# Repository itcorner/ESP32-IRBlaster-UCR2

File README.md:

# ESP32 IR blaster for the Unfolded Circle Remote Two.

This project implements the [Unfolded Circle Remote Two](https://www.unfoldedcircle.com/) dock API to add additional IR blasters
to your remote setup.

This allows the installation of an IR blaster in an independant location from where your
remote and charging dock are located. For example, in an equipment rack or cupboard, or for
multi-room setups.

⚠️ Since Unfolded Circle has released their dock firmware I have not yet updated the software in this repo for Hardware v0.3. Use koeblaster brach in [this repo](https://github.com/itcorner/ucd2-firmware/tree/koeblaster) in the meanwhile.

## Requirements

1. An [Unfolded Circle Remote Two](https://www.unfoldedcircle.com/).
1. An supported ESP32 hardware (see Section [Supported Electronics](#supported-electronics))
1. [PlatformIO](https://platformio.org/) to build and upload firmware
1. Depending on used hardware: Some basic soldering / breadboarding skills and basic understanding of electronic.
1. Depending on used hardware: Some basic electronic parts and IR led.

## Getting Started

1. Clone project from Github and add to PlatformIO.
2. Select the build environment matching your dock hardware.
    - Add your specific board to ``platformio.ini``. Feel free to contribute this back as a pull-request.
3. If required, modify pin mappings in ``lib/config/blaster_config.h``, or by setting `-D defines` in the ``build_flags`` section of your build environment in ``platformio.ini``, respectively (see section [Customizing Pinout/Configuration](#customizing-pinout-configuration)).
    -  For enabling the *learning of IR codes* make sure you have added ``-DBLASTER_ENABLE_IR_LEARN=true`` to the build_flags of your used PlatformIO environment (or in blaster_config.h) and check the assigned GPIO pin.
    -  **Note:** IR learning feature is still under development and tested only with some basic IR codes.
4. Build *firmware* and *filesystem image* via PlattformIO actions for your target hardware.
5. Upload *firmware* and *filesystem image* to your ESP32 hardware (**Hint:** make sure no serial monitor is active during filesystem upload, otherwise upload will fail!).
    -  Details about SPIFFS filesystem image can be found in the respective [Section](#spiffs-filesystem-image)
6. Start discovering process on your Remote Two. The dock should be detected.
7. Perform setup process for dock via Remote Two.
8. Check serial logging for debugging.

⚠️ Do not forget to select the dock as "IR output device" in the configuration of your remotes!

## Customizing Pinout/Configuration 

The following defines are available in ``lib/config/blaster_config.h`` and can be overwritten by setting ``build_flags`` in ``platformio.ini``.

| Define | Description | Options |
|:-------|:------------|:--------|
|`BLASTER_INDICATOR_MODE` | Defines the type of indicator led used for custom dock | `INDICATOR_OFF` no indicator led available<br/>`INDICATOR_LED` single color led (__default__)<br/>`INDICATOR_PIXEL` digital RGB neopixel led |
|`BLASTER_PIN_INDICATOR` | Defines GPIO pin where indicator led is connected to  | Default: `5`<br/>Has no effect if `BLASTER_INDICATOR_MODE=INDICATOR_OFF` |
|`BLASTER_ENABLE_IR_INTERNAL` | Enables/Disables internal IR channel of dock | `true` channel is enabled (__default__)<br/> `false` channel is disabled |
|`BLASTER_PIN_IR_INTERNAL` | Defines GPIO pin of internal IR channel | Default: `12`<br/>Has no effect if `BLASTER_ENABLE_IR_INTERNAL=false` |
|`BLASTER_ENABLE_IR_OUT_1` | Enables/Disables external IR channel 1 of dock | `true` channel is enabled (__default__)<br/> `false` channel is disabled |
|`BLASTER_PIN_IR_OUT_1` | Defines GPIO pin of external IR channel 1 | Default: `13`<br/>Has no effect if `BLASTER_ENABLE_IR_OUT_1=false` |
|`BLASTER_ENABLE_IR_OUT_2` | Enables/Disables external IR channel 2 of dock | `true` channel is enabled (__default__)<br/> `false` channel is disabled |
|`BLASTER_PIN_IR_OUT_2` | Defines GPIO pin of external IR channel 2 | Default: `14`<br/>Has no effect if `BLASTER_ENABLE_IR_OUT_2=false` |
|`BLASTER_ENABLE_IR_LEARN` | Enables/Disables learning of IR codes by an IR receiver | `true` learning is enabled<br/> `false` learning is disabled  (__default__)|
|`BLASTER_PIN_IR_LEARN` | Defines GPIO pin IR receiver is connected to | Default: `16`<br/>Has no effect if `BLASTER_ENABLE_IR_LEARN=false` |
|`BLASTER_ENABLE_ETH` | Enables/Disables an wired Ethernet interface<br/>Currently only Olimex Boards supported. | `true` Ethernet interface available. Requires definition of `OLIMEX_ESP`<br/> `false` Ethernet interface not available  (__default__)|
|`OLIMEX_ESP` | Defines ESP32 package used in Olimex POE Board<br/>Impacts the pins for ethernet interface | `WROOM` tested and confirmed working<br/>`WROVER` untested ⚠️, therefore breaks build on purpose. Adaption in `eth_service.cpp` required!<br/>Has no effect if `BLASTER_ENABLE_ETH=false` |
|`BLASTER_ENABLE_OTA` | Enables Arduino OTA flashing.<br/>**Note**: This OTA function has nothing to do with firmware updates via Remote Two! | `true` OTA flashing is enabled <br/>`false` OTA flashing is not enabled (__default__)| 

## SPIFFS Filesystem Image

For providing details about the dock via a web user interface, files stored in an SPIFF file system are used.
The actual content of the SPIFFS filesystem image is the `data` directory of the project.

`data/spiffs_manifest.json` holds an index about all available files and their expected MD5 sums.
During boot, the dock will check availability of all files listed in the index and validate their checksum.

⚠️ Currently, the `fs_service` will only allow access to files mentioned in the index and available in the filesystem image, irrespecive of the checksum validataion. This might change in future.

**Hint:** In `tools/update_spiffs_manifest.py` a Python script is available to update the contents and MD5-checksums of the filesystem image index. Make sure the script is executed from the project's main folder.

# Supported Electronics

## KoeBlaster Hardware

*KoeBlaster* is designed to be a drop-in replacement of the Logitech Harmony Hub PCB working with Remote Two.

Schematic is tested and working. Comments are of course appreciated!

PCB is manufactured and working. 

[Manufacturing Data](kicad/KoeBlaster/exports) is available in the repository.

⚠️ When manufacturing, make sure you are using a **PCB height of 1mm**, as otherwise the mounting inside the Harmony Hub are not fitting. ⚠️

### Change History

| Revision | Changes | Known-Issues | 
|:-------|:------------|:------------|
| 0.3 | Supporting SMD or THT leds, split top and side led control, optimized BOM for JLCPCB manufacturing | none (yet) |
| 0.2 | fixes of hw problems from v0.1 | none (yet) |
| 0.1 | initial design | value of current limitation resistors for IR leds too high.<br/>short-circuits on external blaster sockets.<br/>CH340 outputs voltages higher than 3.3V, therefore problems with hardware reset circuit. |

### Schematic

### Board

#### Top

#### Bottom

## Olimex ESP32-PoE-ISO + MOD-IRDA

Olimex offers some nice modules for people wanting Plug&Play solutions. 
Using the PlattformIO Environment `env:olimex_poe_iso` the pins shall already be pre-configured correctly for use with the MOD-IRDA extension board.

⚠️ From Olimex two IRDA add-ons are available (MOD-IRDA and MOD-IRDA+). Only MOD-IRDA is supported by this project! Due to different interfacing MOD-IRDA+ add-on is not compatible! ⚠️

### Customizing the pinout 

If you need to change the pinout feel free to do so. Here are the pins configured for the Olimex Board per default:

| Setting | Description |
|:-------|:------------|
|`BLASTER_INDICATOR_MODE` = `INDICATOR_OFF` | Olimex Board does not offer a led for custom usage, therfore indicator is turned off | 
|`BLASTER_ENABLE_IR_INTERNAL` = `true` | Enables internal IR channel of dock used by MOD-IRDA add-on |
|`BLASTER_PIN_IR_INTERNAL` = `4` | GPIO 4 is wired to UEXT header and used by IR sender on MOD-IRDA add-on |
|`BLASTER_ENABLE_IR_OUT_1` = `false` | Disables external IR channel 1 of dock by default. <br/>If you plan to add external circuity set to `true` and configure `BLASTER_PIN_IR_OUT_1` accordingly (only `GPIO0-31` are supproted) |
|`BLASTER_ENABLE_IR_OUT_2` = `false` | Disables external IR channel 2 of dock by default. <br/>If you plan to add external circuity set to `true` and configure `BLASTER_PIN_IR_OUT_2` accordingly (only `GPIO0-31` are supproted) |
|`BLASTER_ENABLE_IR_LEARN` = `true`  | Enables learning of IR codes by an IR receiver | 
|`BLASTER_PIN_IR_LEARN` = `36` | GPIO 36 is wired to UEXT header and used by IR receiver on MOD-IRDA add-on |
|`BLASTER_ENABLE_ETH` = `true` | Enables the wired Ethernet interface of Olimex board | 
|`OLIMEX_ESP` = `WROOM` | Defines ESP32 package used in Olimex POE Board. Currently only `WROOM` is tested and confirmed working<br/>`WROVER` untested ⚠️, therefore breaks build on purpose. Adaption in `eth_service.cpp` required!<br/>Has no effect if `BLASTER_ENABLE_ETH=false` |

### Links to Olimex product pages

[Olimex PoE Iso Board](https://www.olimex.com/Products/IoT/ESP32/ESP32-POE-ISO/open-source-hardware)

[Olimex MOD-IRDA](https://www.olimex.com/Products/Modules/Interface/MOD-IRDA/open-source-hardware)

## DIY Breadboard Example

At least one IR led + transistors and resistors is required for this to operate correctly.
IR learning was tested with an CHQ1838 Infrared receiver module.

Schematic (⚠️ needs update for IR learning!):

# Integrating with the remote

In the remote web interface:

1. Select *Integrations & docks*
1. Under *Docks* click *+*
1. Click on *Discover Docks*
1. Dock should be recognized either via Bluetooth or via WiFi/Ethernet
1. If recognized via Bluetooth, you have to mandatorily specify Wifi settings during adoption process.
1. Click *Next*
1. The blaster should be added as a new dock. If there were issues, then download the recent log files in
*Settings* / *Development* / *Logs*. There should be a reason for any failures logged by the remote.
1. For debugging, the blaster also provides extensive logging output via the serial interface.

# Caveats

The Unfolded Circle Remote Two API, while [documented](https://github.com/unfoldedcircle/core-api/blob/main/dock-api/README.md),
the API could change with a remote update before this library is updated. 

This project is not from Unfolded Circle, so do not ask for support there.

This is just a minimal implementation, and doesn't not support OTA updates, web config, etc at this stage.

The Unfolded Circle web interface will report an error when attempting to check for firmware updates. This is normal as
the remote does not know about this particular dock.

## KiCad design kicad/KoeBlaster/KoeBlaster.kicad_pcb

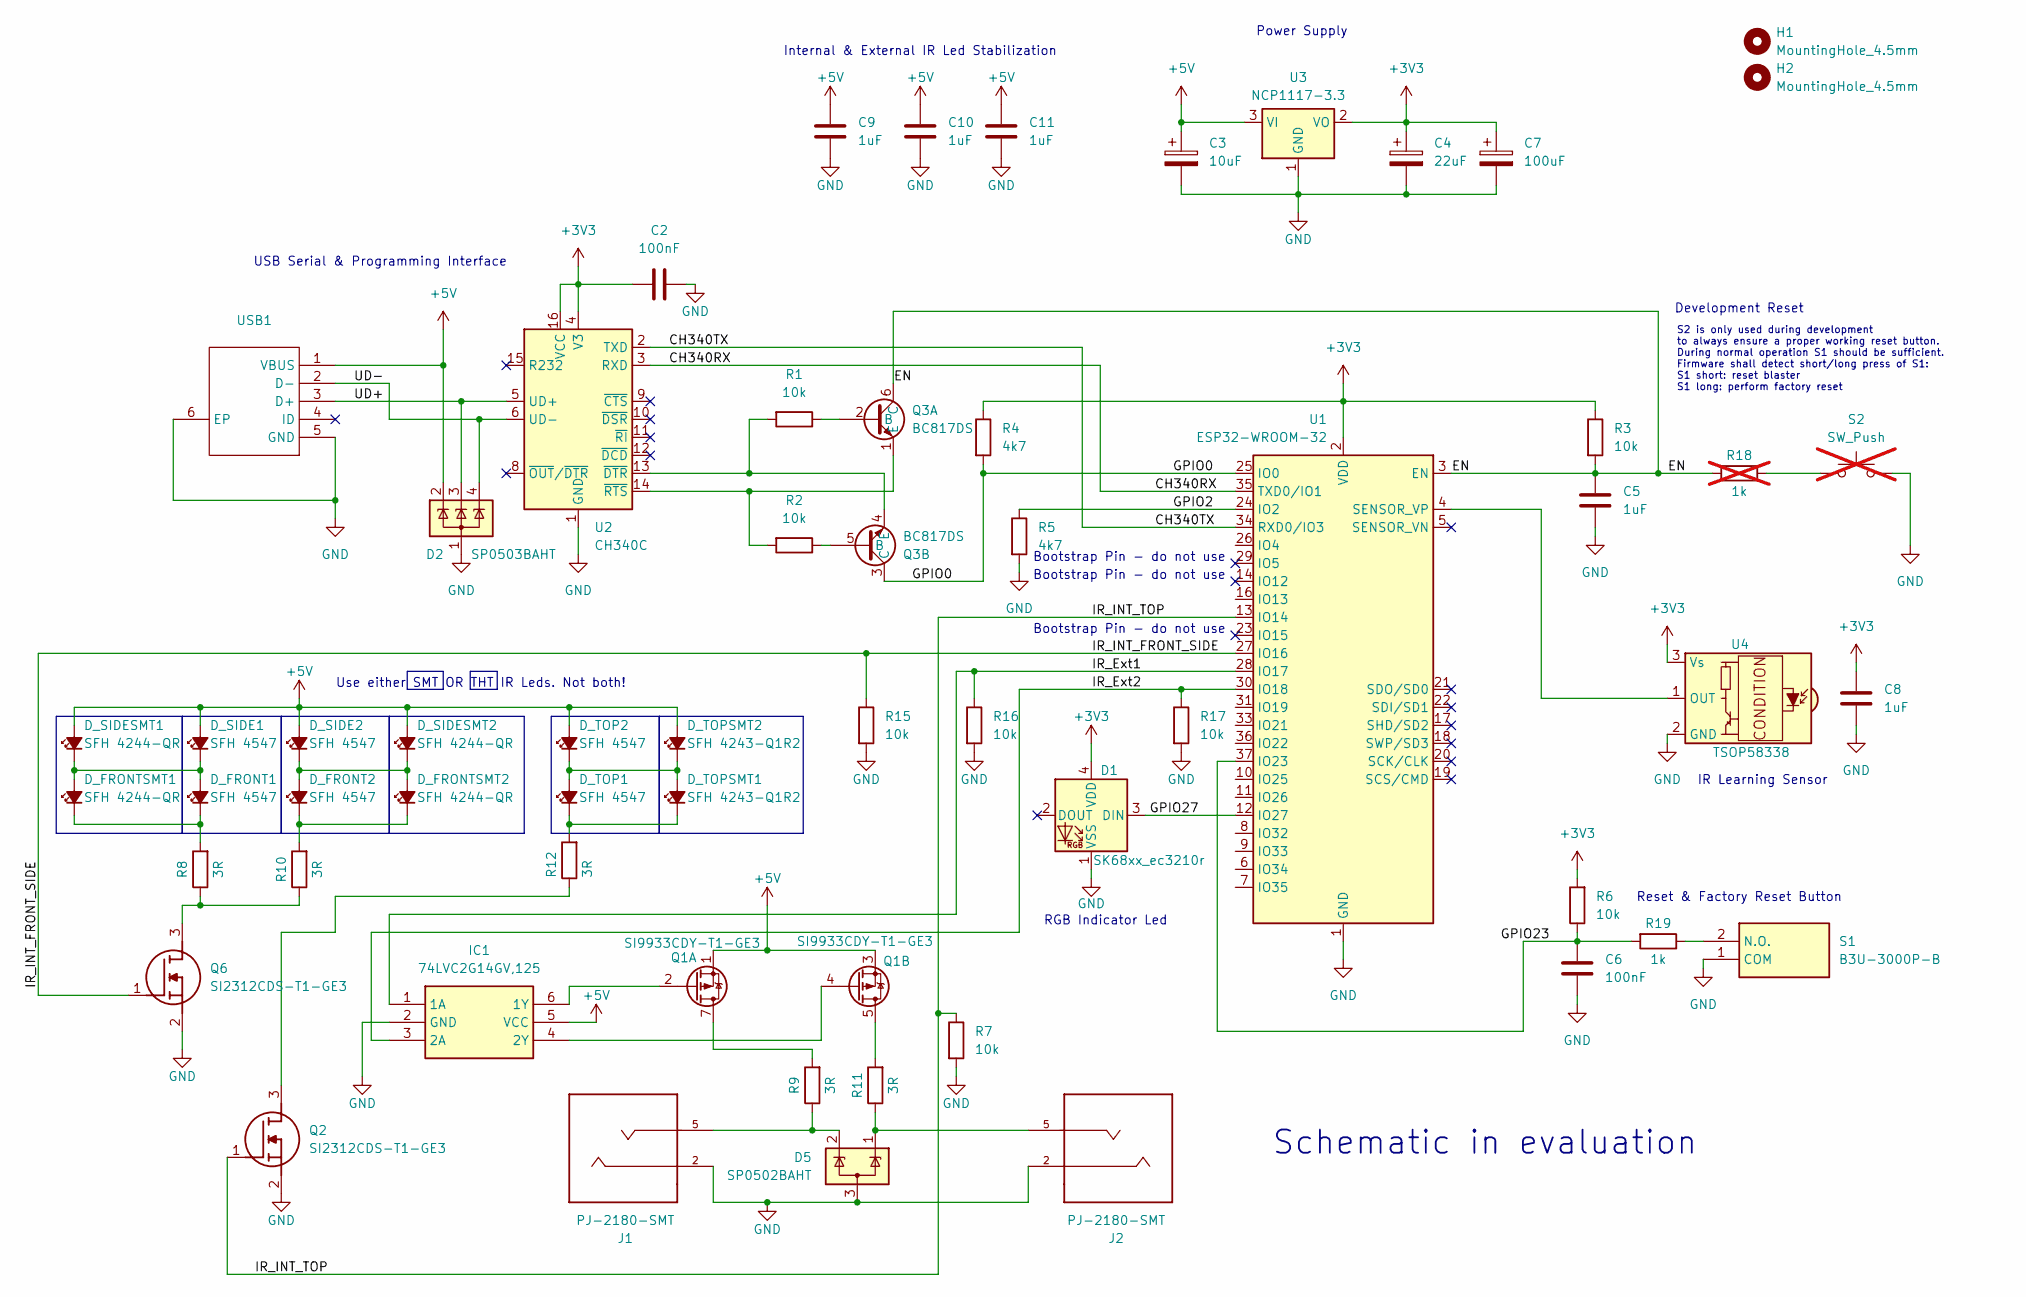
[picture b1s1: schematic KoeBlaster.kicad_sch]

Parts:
C2, C6: 100nF; C_0805_2012Metric_Pad1.18x1.45mm_HandSolder
C3: 10uF; CP_EIA-3216-18_Kemet-A_Pad1.58x1.35mm_HandSolder
C4: 22uF; CP_EIA-3216-18_Kemet-A_Pad1.58x1.35mm_HandSolder
C5, C8, C9, C10, C11: 1uF; C_0805_2012Metric_Pad1.18x1.45mm_HandSolder
C7: 100uF; CP_EIA-3528-12_Kemet-T_Pad1.50x2.35mm_HandSolder
D1: SK68xx_ec3210r; SK68xx-EC3210R
D2: SP0503BAHT; SOT-143
D5: SP0502BAHT; SOT-23
D_FRONT1, D_FRONT2: SFH 4547; LED_D5.0mm_Horizontal_O6.35mm_Z3.0mm
D_FRONTSMT1, D_FRONTSMT2: SFH 4244-QR; LED_SFH_4244-QR-Z
D_SIDE1, D_SIDE2: SFH 4547; LED_D5.0mm_Horizontal_O6.35mm_Z3.0mm
D_SIDESMT1, D_SIDESMT2: SFH 4244-QR; LED_SFH_4244-QR-Z
D_TOP1, D_TOP2: SFH 4547; LED_D5.0mm_IRBlack
D_TOPSMT1, D_TOPSMT2: SFH 4243-Q1R2; LEDM3528X210N
H1, H2: MountingHole_4.5mm
IC1: 74LVC2G14GV,125; SOT95P275X110-6N; Mouser Part Number 771-LVC2G14GV125
J1, J2: PJ-2180-SMT
Q1: SI9933CDY-T1-GE3; SOIC-8_3.9x4.9mm_P1.27mm
Q2, Q6: SI2312CDS-T1-GE3; SOT95P237X112-3N; Manufacturer_Part_Number SI2312CDS-T1-GE3
Q3: BC817DS; SOT95P275X110-6N; Mouser Part Number 771-BC817DSF
R1, R2, R3, R6, R7, R15, R16, R17: 10k; R_0805_2012Metric_Pad1.20x1.40mm_HandSolder
R4, R5: 4k7; R_0805_2012Metric_Pad1.20x1.40mm_HandSolder
R8, R9, R10, R11, R12: 3R; R_0805_2012Metric_Pad1.20x1.40mm_HandSolder
R18: 1k; R_0805_2012Metric_Pad1.20x1.40mm_HandSolder; not fitted
R19: 1k; R_0805_2012Metric_Pad1.20x1.40mm_HandSolder
S1: B3U-3000P-B; B3U3000PB; Mouser Part Number 653-B3U-3000P-B
S2: SW_Push; SW_SPST_B3U-1000P; not fitted
U1: ESP32-WROOM-32
U2: CH340C; SOIC-16_3.9x9.9mm_P1.27mm
U3: NCP1117-3.3; SOT-223-3_TabPin2
U4: TSOP58338; Vishay_MINICAST-3Pin
USB1: USB_B_Mini; MICRO-USB-SMD_BTC-TC5T-23; Manufacturer Part BTC-TC5T-23; LCSC Part Name Micro-B 母 卧贴

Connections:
+3V3: C2.1, C4.1, C7.1, C8.1, D1.4 (VDD), R3.1, R4.1, R6.2, U1.2 (VDD), U2.4 (V3), U2.16 (VCC), U3.2 (VO), U4.3 (Vs)
+5V: C3.1, C9.1, C10.1, C11.1, D2.2 (K), D_SIDE1.2 (A), D_SIDE2.2 (A), D_SIDESMT1.2 (A), D_SIDESMT2.2 (A), D_TOP2.2 (A), D_TOPSMT2.2 (A), IC1.5 (VCC), Q1.1 (S1), Q1.3 (S2), U3.3 (VI), USB1.1 (VBUS)
/CH340RX: U1.35 (TXD0/IO1), U2.3 (RXD)
/CH340TX: U1.34 (RXD0/IO3), U2.2 (TXD)
/EN: C5.1, Q3.6 (C), R3.2, R18.2, U1.3 (EN)
/GPIO0: Q3.3 (C), R4.2, U1.25 (IO0)
/GPIO2: R5.1, U1.24 (IO2)
/GPIO23: C6.1, R6.1, R19.2, U1.37 (IO23)
/GPIO27: D1.3 (DIN), U1.12 (IO27)
/IR_Ext1: IC1.1 (1A), R16.1, U1.28 (IO17)
/IR_Ext2: IC1.3 (2A), R17.1, U1.30 (IO18)
/IR_INT_FRONT_SIDE: Q6.1 (G), R15.1, U1.27 (IO16)
/IR_INT_TOP: Q2.1 (G), R7.1, U1.13 (IO14)
/UD+: D2.3 (K), U2.5 (UD+), USB1.3 (D+)
/UD-: D2.4 (K), U2.6 (UD-), USB1.2 (D-)
GND: C2.2, C3.2, C4.2, C5.2, C6.2, C7.2, C8.2, C9.2, C10.2, C11.2, D1.1 (VSS), D2.1 (A), D5.3 (A), IC1.2 (GND), J1.2, J2.2, Q2.2 (S), Q6.2 (S), R5.2, R7.2, R15.2, R16.2, R17.2, S1.1 (COM), S2.2, U1.1 (GND), U1.15 (GND), U1.38 (GND), U1.39 (GND), U2.1 (GND), U3.1 (GND), U4.2 (GND), USB1.5 (GND), USB1.6 (EP)
unnamed: D5.1 (K), J2.5, R11.1
unnamed: D5.2 (K), J1.5, R9.1
unnamed: D_FRONT1.2 (A), D_FRONTSMT1.2 (A), D_SIDE1.1 (K), D_SIDESMT1.1 (K)
unnamed: D_FRONT1.1 (K), D_FRONTSMT1.1 (K), R8.2
unnamed: D_FRONT2.2 (A), D_FRONTSMT2.2 (A), D_SIDE2.1 (K), D_SIDESMT2.1 (K)
unnamed: D_FRONT2.1 (K), D_FRONTSMT2.1 (K), R10.2
unnamed: D_TOP1.2 (A), D_TOP2.1 (K), D_TOPSMT1.2 (A), D_TOPSMT2.1 (K)
unnamed: D_TOP1.1 (K), D_TOPSMT1.1 (K), R12.2
unnamed: IC1.6 (1Y), Q1.2 (G1)
unnamed: IC1.4 (2Y), Q1.4 (G2)
unnamed: Q1.7 (D1), Q1.8 (D1), R9.2
unnamed: Q1.5 (D2), Q1.6 (D2), R11.2
unnamed: Q2.3 (D), R12.1
unnamed: Q3.2 (B), R1.1
unnamed: Q3.1 (E), R2.2, U2.14 (~RTS)
unnamed: Q3.5 (B), R2.1
unnamed: Q3.4 (E), R1.2, U2.13 (~DTR)
unnamed: Q6.3 (D), R8.1, R10.1
unnamed: R18.1, S2.1
unnamed: R19.1, S1.2 (N.O.)
unnamed: U1.4 (SENSOR_VP), U4.1 (OUT)

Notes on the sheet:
Internal & External IR Led Stabilization
RGB Indicator Led
S2 is only used during development to always ensure a proper working reset button. During normal operation S1 should be sufficient. Firmware shall detect short/long press of S1: S1 short: reset blaster S1 long: perform factory reset
Use either SMT OR THT IR Leds. Not both!
Development Reset
USB Serial & Programming Interface
Reset & Factory Reset Button
Bootstrap Pin - do not use
Schematic in evaluation
Power Supply
IR Learning Sensor

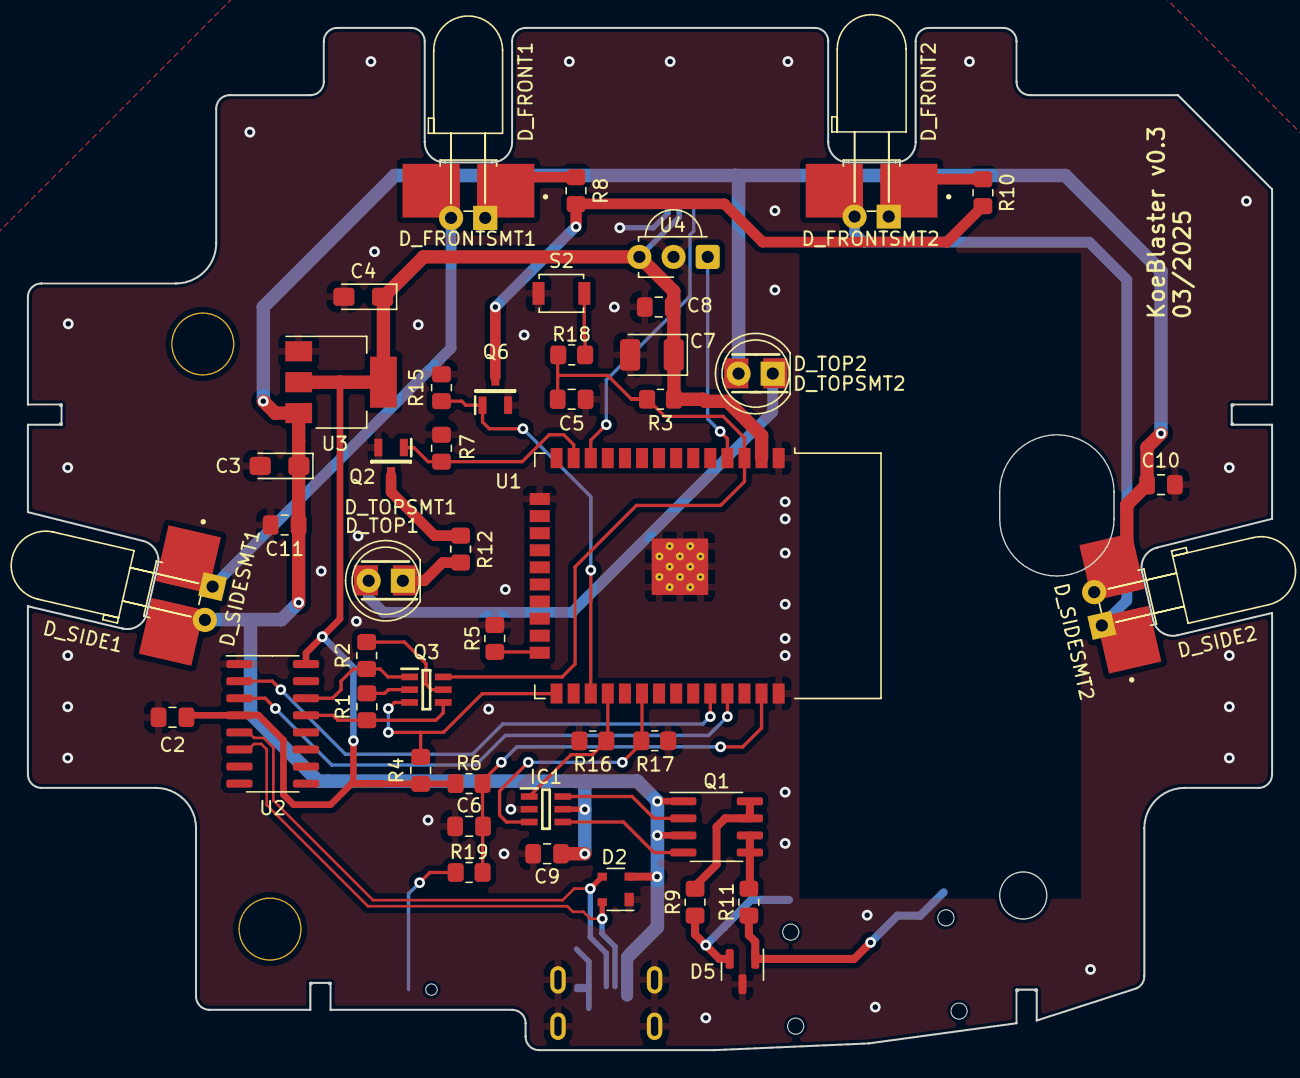
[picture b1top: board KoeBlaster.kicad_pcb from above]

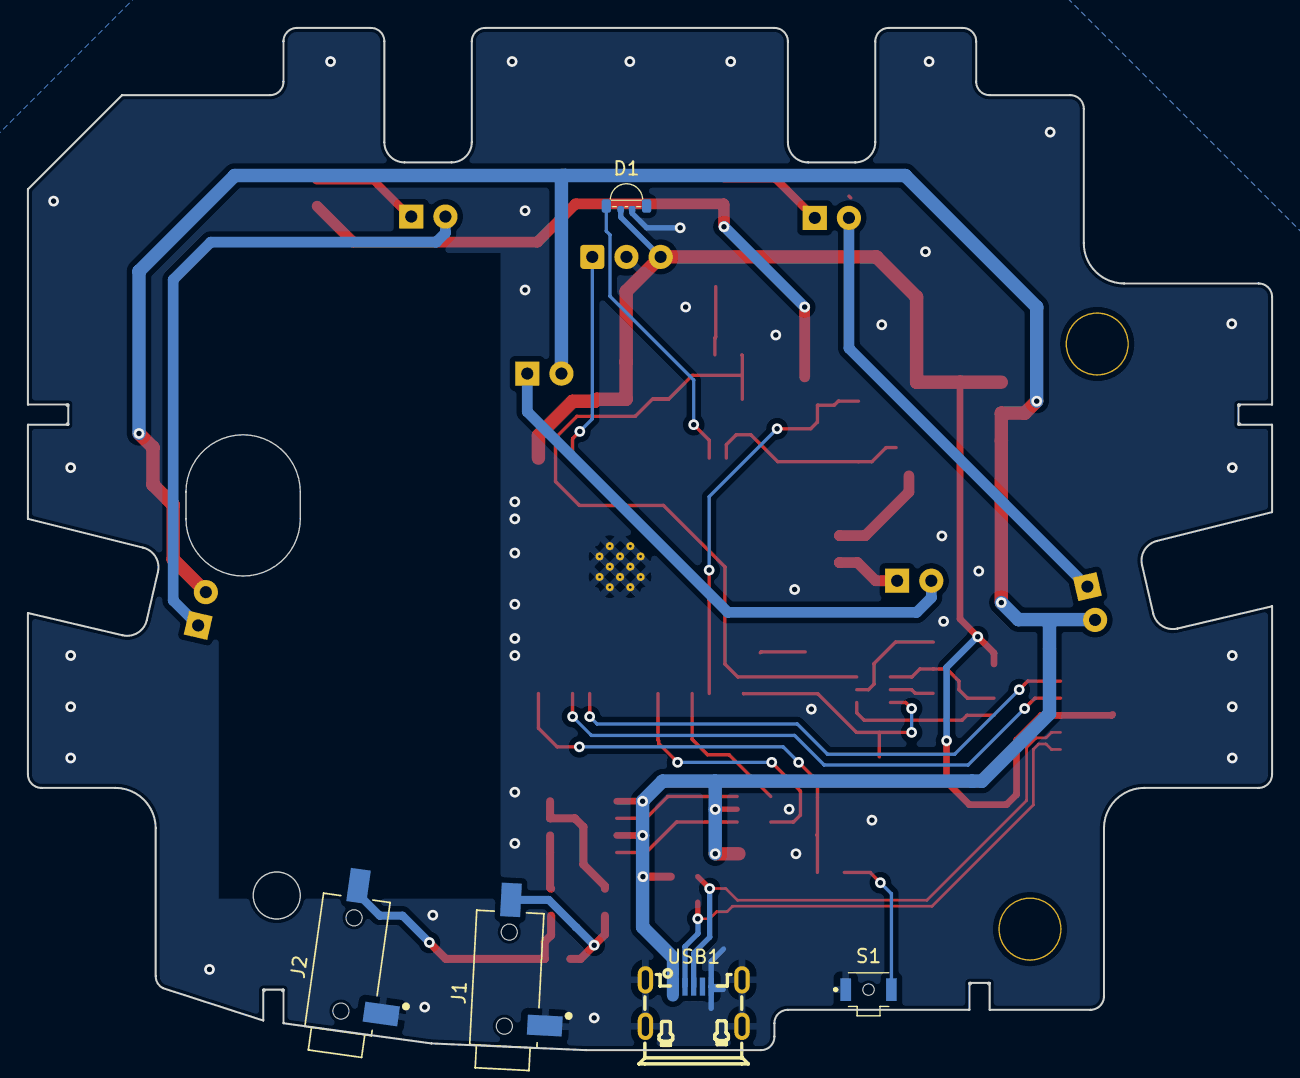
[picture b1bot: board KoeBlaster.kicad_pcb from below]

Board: 2 copper layers, 92.5 x 76.0 mm, 58 parts (5 on the bottom side), 37 nets.

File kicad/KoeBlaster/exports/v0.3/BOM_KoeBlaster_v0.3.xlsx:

ID | Bezeichner | Footprint | StÃ¼ckzahl | Bezeichnung | Anbieter und Referenz | JLCPCB Part# | JLCPCB Info | JCLPCB Manufacturer | JLCPCB MFR Number
1 | C9,C11,C10,C8,C5 | C_0805_2012Metric_Pad1.18x1.45mm_HandSolder | 5 | 1uF |  | C24123 | 16V 1uF X7R ±10% 0805 Multilayer Ceramic Capacitors MLCC - SMD/SMT ROHS | Samsung Electro-Mechanics | CL21B105KOFNNNE
2 | J2,J1 | PJ-2180-SMT | 2 | PJ-2180-SMT |  | C2885001 | -20℃~+70℃ 2.5mm headphone jack 235℃ 30V 500mA SMD Audio Connectors (Headphones)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 | XKB Connection | PJ-2180-SMT
3 | U1 | ESP32-WROOM-32 | 1 | ESP32-WROOM-32 |  | C701343 | SMD,18x25.5mm WiFi Modules ROHS | Espressif Systems | ESP32-WROOM-32E-N16
4 | IC1 | SOT95P275X110-6N | 1 | 74LVC2G14GV,125 |  | C426708 | Schmitt Trigger 2 4uA 4.3ns@5V,50pF 1.65V~5.5V TSOP-6-1.5mm Inverters ROHS | Nexperia | 74LVC2G14GV,125
6 | D2 | SOT-143 | 1 | SP0503BAHT |  | C2682275 | SOT-143-4 ESD and Surge Protection (TVS/ESD) ROHS | TECH PUBLIC | TPSP0503BAHTG
7 | R9,R10,R11,R8,R12 | R_0805_2012Metric_Pad1.20x1.40mm_HandSolder | 5 | 3R |  | C2828761 | 125mW Thin Film Resistor 150V ±25ppm/℃ ±0.1% 3Ω 0805 Chip Resistor - Surface Mo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 | Viking Tech | ARG05BTC0030
8 | D_FRONT1,D_SIDE1,D_FRONT2,D_SIDE2 | LED_D5.0mm_Horizontal_O6.35mm_Z3.0mm | 4 | SFH 4547
9 | R3,R6,R2,R15,R17,R16,R1,R7 | R_0805_2012Metric_Pad1.20x1.40mm_HandSolder | 8 | 10k |  | C217770 | 125mW Thin Film Resistor 100V ±25ppm/℃ ±1% 10kΩ 0805 Chip Resistor - Surface Mo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 | Viking Tech | ARG05FTC1002
10 | C2,C6 | C_0805_2012Metric_Pad1.18x1.45mm_HandSolder | 2 | 100nF |  | C1711 | 50V 100nF X7R ±10% 0805 Multilayer Ceramic Capacitors MLCC - SMD/SMT ROHS | Samsung Electro-Mechanics | CL21B104KBCNNNC
11 | U4 | Vishay_MINICAST-3Pin | 1 | TSOP58338
12 | D_FRONTSMT1,D_SIDESMT2,D_FRONTSMT2,D_SIDESMT1 | LED_SFH_4244-QR-Z | 4 | SFH 4244-QR
13 | Q1 | SOIC-8_3.9x4.9mm_P1.27mm | 1 | SI9933CDY-T1-GE3 | JLCPCB Alternative used | C5444648 | 30V 2 P-Channel SO-8 MOSFETs ROHS | VBsemi Elec | SI9933CDY-T1-GE3-VB
14 | D_TOP1,D_TOP2 | LED_D5.0mm_IRBlack | 2 | SFH 4547
15 | D5 | SOT-23 | 1 | SP0502BAHT |  | C19829477 | SOT-23 ESD and Surge Protection (TVS/ESD) ROHS | TECH PUBLIC | SP0502BAHTG
16 | Q6,Q2 | SOT95P237X112-3N | 2 | SI2312CDS-T1-GE3 | JLCPCB Alternative used | C784613 | 20V 6.8A 1.2W SOT-23(TO-236) MOSFETs ROHS | FUXINSEMI | FS2312
17 | R5,R4 | R_0805_2012Metric_Pad1.20x1.40mm_HandSolder | 2 | 4k7 |  | C218604 | 125mW Thin Film Resistor 100V ±25ppm/℃ ±1% 4.7kΩ 0805 Chip Resistor - Surface M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 | Viking Tech | ARG05FTC4701
18 | D_TOPSMT2,D_TOPSMT1 | LEDM3528X210N | 2 | SFH 4243-Q1R2
19 | C3 | CP_EIA-3216-18_Kemet-A_Pad1.58x1.35mm_HandSolder | 1 | 10uF |  | C122260 | 10uF 6.3V 4Ω@100kHz ±10% CASE-A-3216-18(mm) Tantalum Capacitors ROHSHigher volt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 | KEMET | T491A106K006AT
20 | C7 | CP_EIA-3528-12_Kemet-T_Pad1.50x2.35mm_HandSolder | 1 | 100uF |  | C122271 | 100uF 10V 1.2Ω@100kHz ±10% CASE-B-3528-21(mm) Tantalum Capacitors ROHSHigher vo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 | KEMET | T491B107K010AT
21 | R19 | R_0805_2012Metric_Pad1.20x1.40mm_HandSolder | 1 | 1k |  | C218388 | 125mW Thin Film Resistor 100V ±25ppm/℃ ±1% 1kΩ 0805 Chip Resistor - Surface Mou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 | Viking Tech | ARG05FTC1001
23 | U3 | SOT-223-3_TabPin2 | 1 | NCP1117-3.3 |  | C26537 | 64dB@(120Hz) 1A Fixed 3.3V Positive electrode 20V SOT-223-3 Voltage Regulators 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 | onsemi | NCP1117ST33T3G
24 | Q3 | SOT95P275X110-6N | 1 | BC817DS |  | C128436 | 45V 600mW 160@100mA,1V 500mA NPN TSOP-6-1.5mm Bipolar (BJT) ROHS | Nexperia | BC817DS,115
25 | C4 | CP_EIA-3216-18_Kemet-A_Pad1.58x1.35mm_HandSolder | 1 | 22uF |  | C139740 | 22uF 10V 2.5Ω@100kHz ±10% CASE-A-3216-18(mm) Tantalum Capacitors ROHS | Vishay Intertech | 293D226X9010A2TE3
26 | U2 | SOIC-16_3.9x9.9mm_P1.27mm | 1 | CH340C |  | C7464026 | SOP-16 USB Converters ROHS | WCH(Jiangsu Qin Heng) | CH340C
27 | S1 | B3U3000PB | 1 | B3U-3000P-B | 9 stk lagernd | C4364471 | Rectangle button 50mA Standing paste SPST 100000 Times 162gf 12V - Tactile Swit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 | Omron Electronics | B3U-3000P-B
28 | D1 | SK68xx-EC3210R | 1 | SK68xx_ec3210r |  | C2890041 | SMD,1.1x3.2mm RGB LEDs(Built-in IC) ROHS | OPSCO Optoelectronics | SK6812D-EC3210R
29 | USB1 | MICRO-USB-SMD_BTC-TC5T-23 | 1 | USB_B_Mini |  | C2908212 | USB 2.0 2A 1 Surface Mount 5 Female -20℃~+85℃ Micro-B SMD USB Connectors ROHS | BZXC | BTC-TC5T-23

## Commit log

2025-04-06 Updated hardware to v0.3
